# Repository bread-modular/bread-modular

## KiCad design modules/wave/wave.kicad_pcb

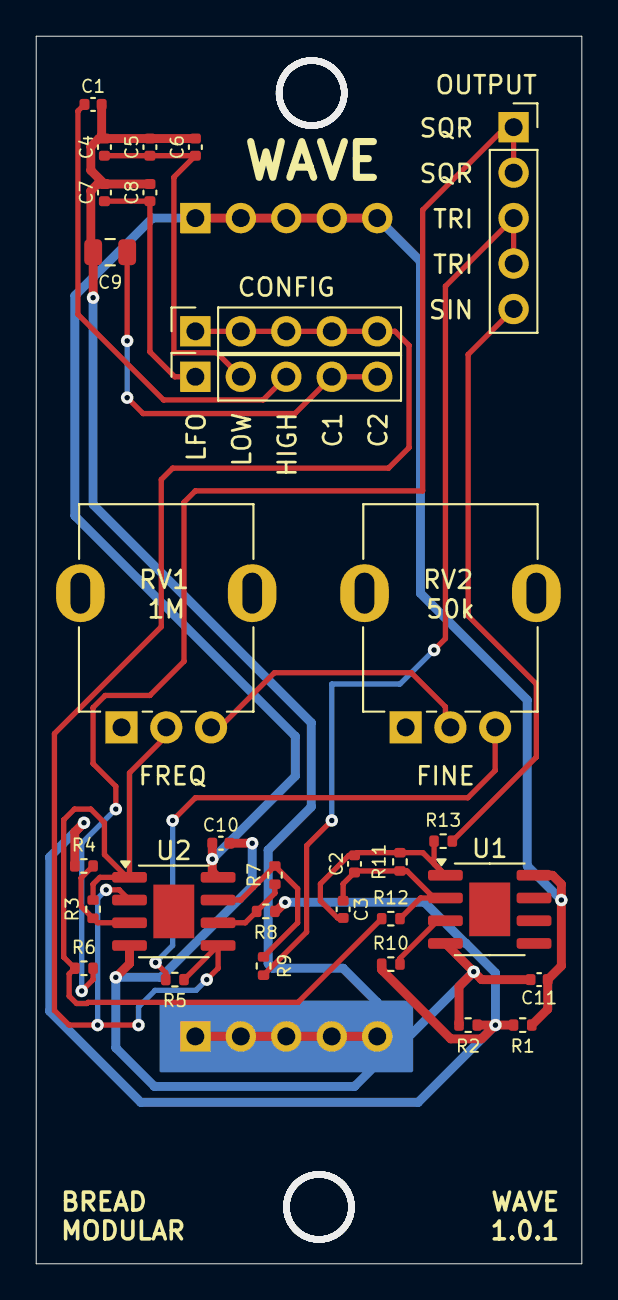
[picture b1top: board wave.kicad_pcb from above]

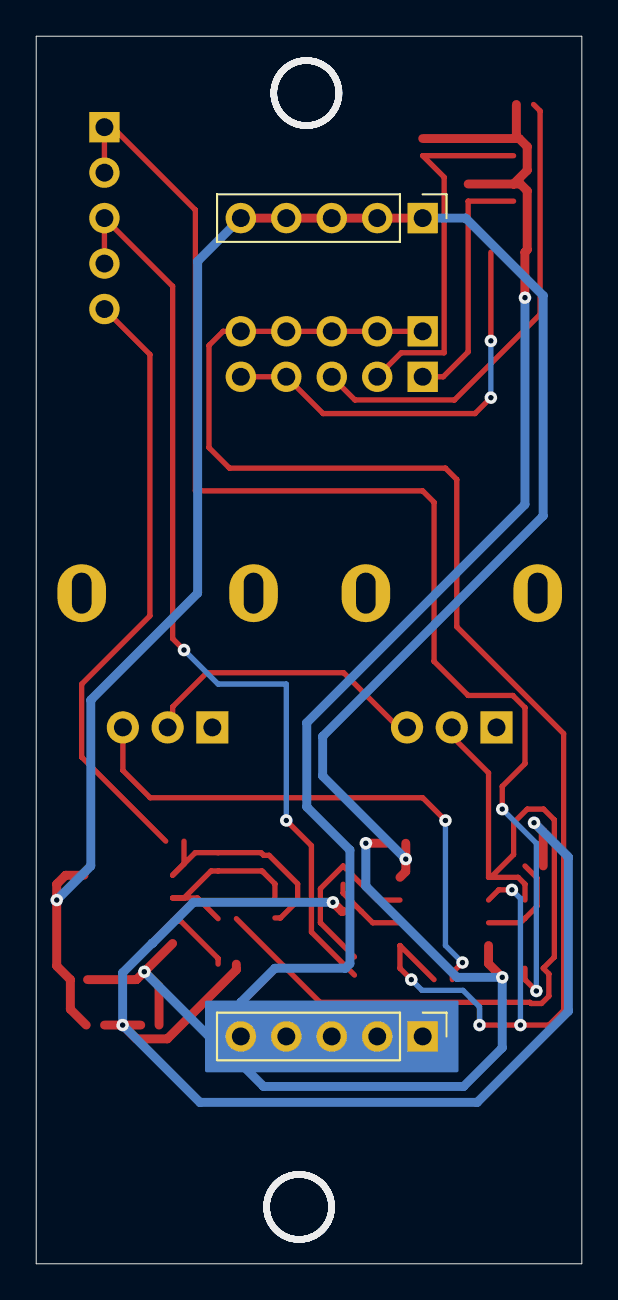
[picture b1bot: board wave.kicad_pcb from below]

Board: 2 copper layers, 30.5 x 68.6 mm, 33 parts (2 on the bottom side), 20 nets.

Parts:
5V1: Conn_01x05_Pin; PinHeader_1x05_P2.54mm_Vertical
C1: 1nf; C_0402_1005Metric
C2, C3, C10, C11: 0.1uf; C_0402_1005Metric
C4, C5, C6: 10nf; C_0402_1005Metric
C7, C8: 1uf; C_0402_1005Metric
C9: 22uf; C_0805_2012Metric
GND1: Conn_01x05_Pin; PinHeader_1x05_P2.54mm_Vertical
INPUT1: Cap Connect; PinSocket_1x05_P2.54mm_Vertical
INPUT2: Caps; PinSocket_1x05_P2.54mm_Vertical
OUTPUT2: Output Waves; PinSocket_1x05_P2.54mm_Vertical
R1, R2, R6, R9, R13: 1k; R_0402_1005Metric
R3, R4, R7, R8, R10, R11: 100k; R_0402_1005Metric
R5, R12: 10k; R_0402_1005Metric
RV1: 1M; Potentiometer_RV09
RV2: 50k; Potentiometer_RV09
U1, U2: MCP6002-xSN; SOIC-8-1EP_3.9x4.9mm_P1.27mm_EP2.29x3mm

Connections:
+2.5V: R1.2, R2.1, R4.1, R8.1, R10.1
+5V: 5V1.1, 5V1.2, 5V1.3, 5V1.4, 5V1.5, C10.1, C11.1, R1.1, U1.8 (V+), U2.8 (V+)
CAP_CONNECT: INPUT1.1, INPUT1.2, INPUT1.3, INPUT1.4, INPUT1.5, R5.1, U2.2 (-), U2.5 (+)
CAP_CUSTOM: C9.1, INPUT2.4, INPUT2.5
CAP_HIGH: C1.1, INPUT2.3
CAP_LFO: C7.1, C8.1, INPUT2.1
CAP_LOW: C4.1, C5.1, C6.1, INPUT2.2
GND: C1.2, C4.2, C5.2, C6.2, C7.2, C8.2, C9.2, C10.2, C11.2, GND1.1, GND1.2, GND1.3, GND1.4, GND1.5, R2.2, U1.4 (V-), U2.4 (V-)
unnamed: C2.2, C3.2, R11.2, R13.1, U1.1
unnamed: R5.2, RV2.3
unnamed: R7.2, R9.1, U2.7
unnamed: RV1.3, RV2.2
unnamed: R10.2, U1.3 (+)
unnamed: C2.1, C3.1, R11.1, R12.2, U1.2 (-)
unnamed: R3.1, R4.2, U2.3 (+)
unnamed: R7.1, R8.2, U2.6 (-)
OPAMP_SQUARE: R3.2, R6.1, R12.1, RV1.2, U2.1
OUT_SINE: OUTPUT2.5, R13.2
OUT_SQUARE: OUTPUT2.1, OUTPUT2.2, R6.2
OUT_TRI: OUTPUT2.3, OUTPUT2.4, R9.2

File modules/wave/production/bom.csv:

Designator,Footprint,Quantity,Value,LCSC Part #
"5V1, GND1",PinHeader_1x05_P2.54mm_Vertical,2,Conn_01x05_Pin,
C1,0402,1,1nf,
"C10, C11, C2, C3",0402,4,0.1uf,
"C4, C5, C6",0402,3,10nf,
"C7, C8",0402,2,1uf,
C9,0805,1,22uf,
INPUT1,PinSocket_1x05_P2.54mm_Vertical,1,Cap Connect,
INPUT2,PinSocket_1x05_P2.54mm_Vertical,1,Caps,
OUTPUT2,PinSocket_1x05_P2.54mm_Vertical,1,Output Waves,
"R1, R13, R2, R6, R9",0402,5,1k,
"R10, R11, R3, R4, R7, R8",0402,6,100k,
"R12, R5",0402,2,10k,
RV1,Potentiometer_RV09,1,1M,
RV2,Potentiometer_RV09,1,50k,
"U1, U2",SOIC-8-1EP_3.9x4.9mm_P1.27mm_EP2.29x3mm,2,MCP6002-xSN,

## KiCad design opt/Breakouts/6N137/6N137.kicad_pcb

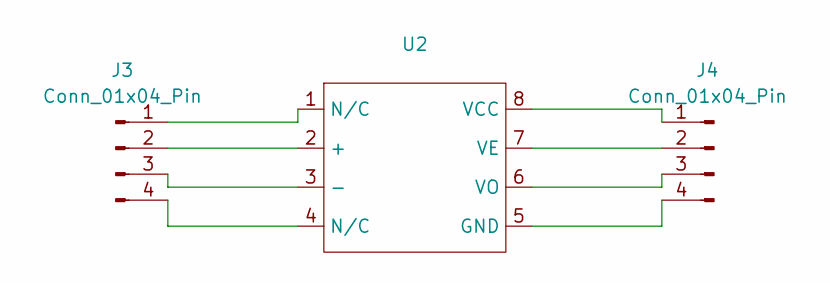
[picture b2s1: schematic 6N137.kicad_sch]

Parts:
J3, J4: Conn_01x04_Pin; PinSocket_1x04_P2.54mm_Vertical
U2: SOIC-8 2.54

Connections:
unnamed: J3.1, U2.1 (N/C)
unnamed: J3.2, U2.2 (+)
unnamed: J3.3, U2.3 (-)
unnamed: J3.4, U2.4 (N/C)
unnamed: J4.1, U2.8 (VCC)
unnamed: J4.2, U2.7 (VE)
unnamed: J4.3, U2.6 (VO)
unnamed: J4.4, U2.5 (GND)

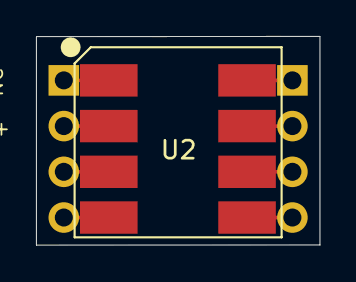
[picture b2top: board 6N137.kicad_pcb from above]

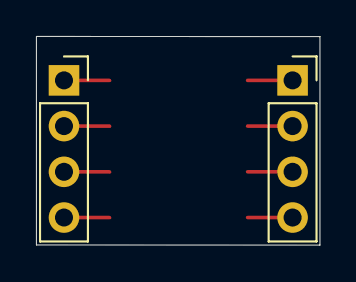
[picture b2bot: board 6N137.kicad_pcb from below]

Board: 2 copper layers, 15.8 x 11.6 mm, 3 parts (2 on the bottom side), 8 nets.

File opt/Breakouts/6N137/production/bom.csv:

Designator,Footprint,Quantity,Value,LCSC Part #
"J3, J4",PinSocket_1x04_P2.54mm_Vertical,2,Conn_01x04_Pin,
U2,SOIC-8 2.54,1,~,

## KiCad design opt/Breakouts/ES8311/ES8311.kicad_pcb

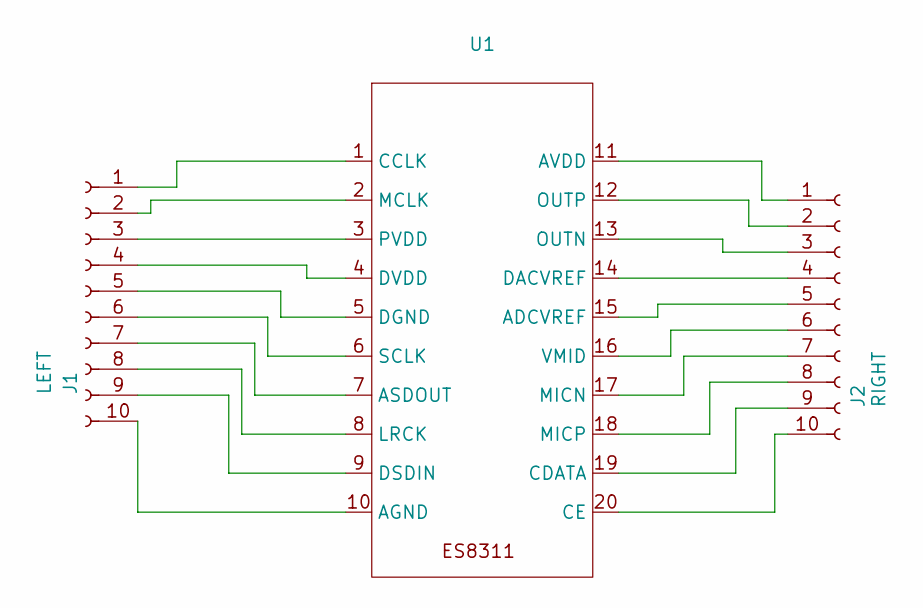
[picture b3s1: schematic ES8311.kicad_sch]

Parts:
J1: LEFT; PinSocket_1x10_P2.54mm_Vertical
J2: RIGHT; PinSocket_1x10_P2.54mm_Vertical
U1: QFN-20-1EP_3x3mm_P0.4mm_EP1.65x1.65mm

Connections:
unnamed: J1.1, U1.1 (CCLK)
unnamed: J1.2, U1.2 (MCLK)
unnamed: J1.3, U1.3 (PVDD)
unnamed: J1.4, U1.4 (DVDD)
unnamed: J1.5, U1.5 (DGND)
unnamed: J1.6, U1.6 (SCLK)
unnamed: J1.7, U1.7 (ASDOUT)
unnamed: J1.8, U1.8 (LRCK)
unnamed: J1.9, U1.9 (DSDIN)
unnamed: J1.10, U1.10 (AGND)
unnamed: J2.1, U1.11 (AVDD)
unnamed: J2.2, U1.12 (OUTP)
unnamed: J2.3, U1.13 (OUTN)
unnamed: J2.4, U1.14 (DACVREF)
unnamed: J2.5, U1.15 (ADCVREF)
unnamed: J2.6, U1.16 (VMID)
unnamed: J2.7, U1.17 (MICN)
unnamed: J2.8, U1.18 (MICP)
unnamed: J2.9, U1.19 (CDATA)
unnamed: J2.10, U1.20 (CE)

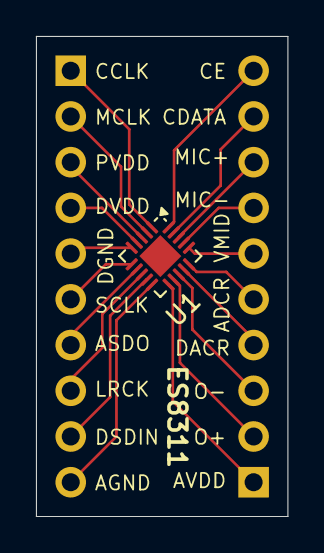
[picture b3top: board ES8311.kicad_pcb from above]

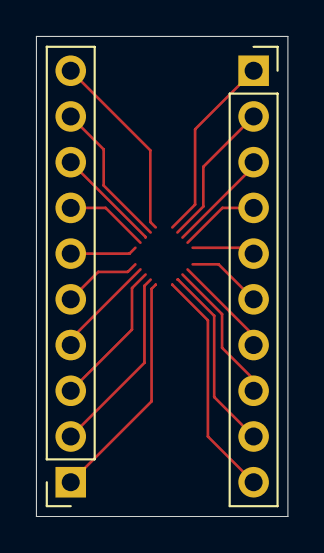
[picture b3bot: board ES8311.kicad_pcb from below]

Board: 2 copper layers, 14.0 x 26.7 mm, 3 parts (2 on the bottom side), 20 nets.

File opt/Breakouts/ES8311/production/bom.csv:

Designator,Footprint,Quantity,Value,LCSC Part #
J1,PinSocket_1x10_P2.54mm_Vertical,1,LEFT,
J2,PinSocket_1x10_P2.54mm_Vertical,1,RIGHT,
U1,QFN-20-1EP_3x3mm_P0.4mm_EP1.65x1.65mm,1,~,

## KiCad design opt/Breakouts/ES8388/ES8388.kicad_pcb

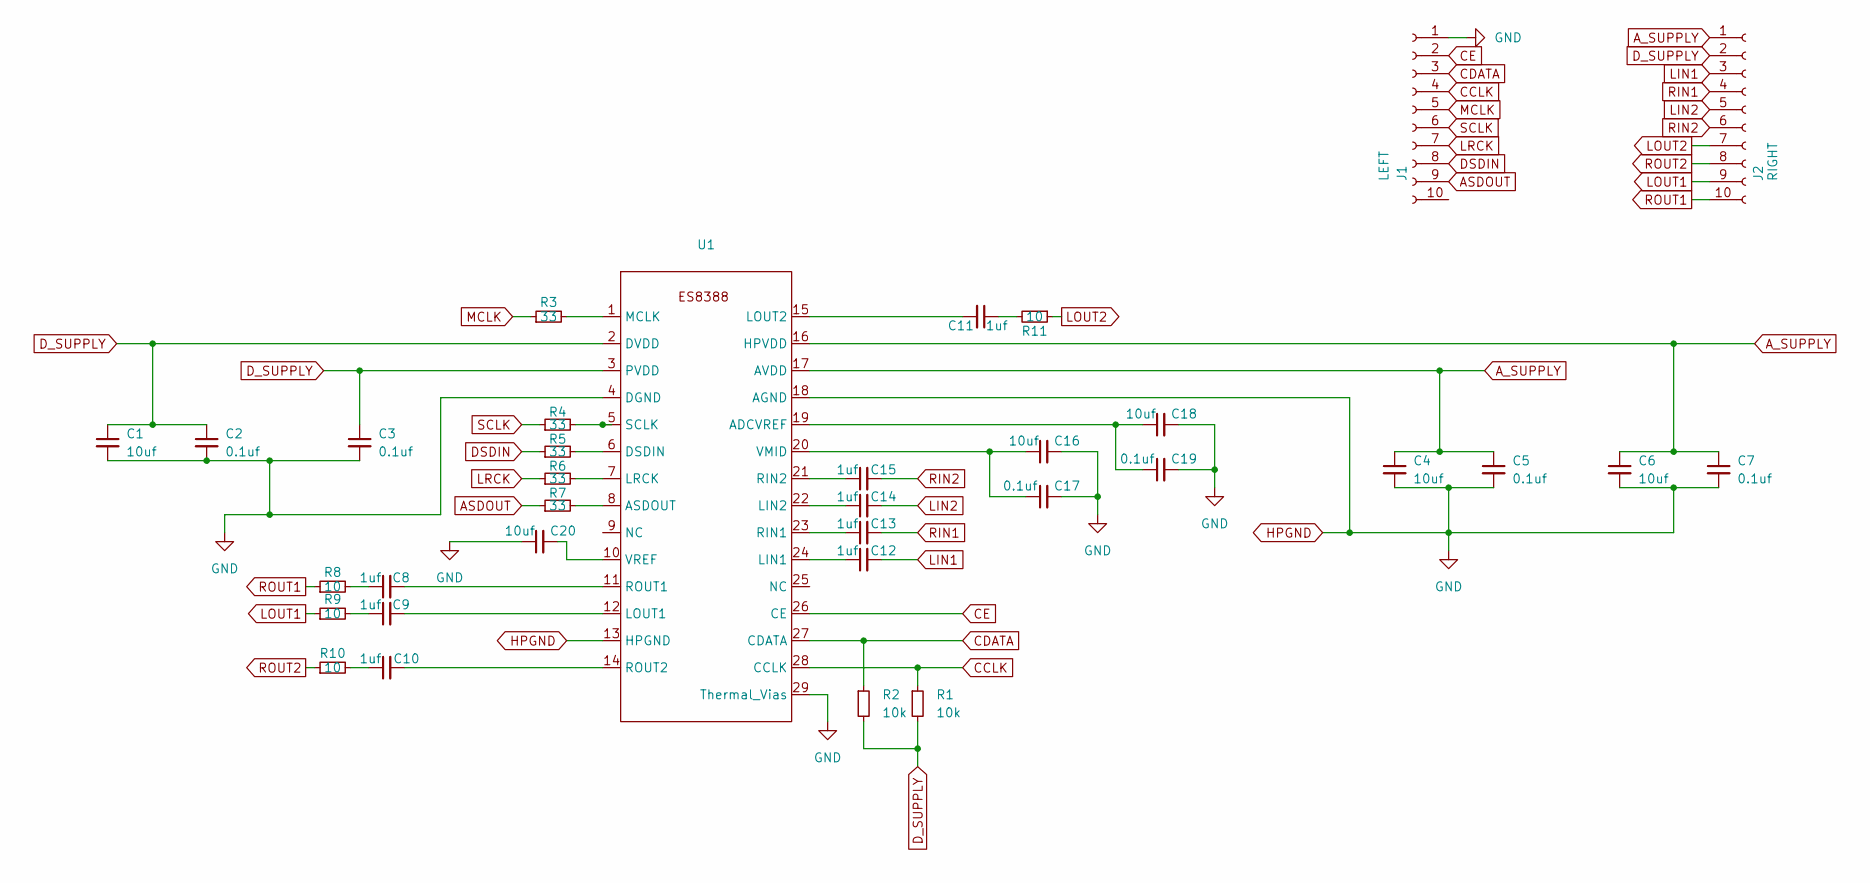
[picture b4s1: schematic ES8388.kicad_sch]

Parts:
C1, C4, C6, C16, C18, C20: 10uf; C_0402_1005Metric
C2, C3, C5, C7, C17, C19: 0.1uf; C_0402_1005Metric
C8, C9, C10, C11, C12, C13, C14, C15: 1uf; C_0402_1005Metric
J1: LEFT; PinSocket_1x10_P2.54mm_Vertical
J2: RIGHT; PinSocket_1x10_P2.54mm_Vertical
R1, R2: 10k; R_0402_1005Metric
R3, R4, R5, R6, R7: 33; R_0402_1005Metric
R8, R9, R10, R11: 10; R_0402_1005Metric
U1: QFN-28-1EP_4x4mm_P0.45mm_EP2.4x2.4mm_ThermalVias

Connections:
ASDOUT: J1.9, R7.1
A_SUPPLY: C4.1, C5.1, C6.1, C7.1, J2.1, U1.16 (HPVDD), U1.17 (AVDD)
CCLK: J1.4, R1.1, U1.28 (CCLK)
CDATA: J1.3, R2.1, U1.27 (CDATA)
CE: J1.2, U1.26 (CE)
DSDIN: J1.8, R5.1
D_SUPPLY: C1.1, C2.1, C3.1, J2.2, R1.2, R2.2, U1.2 (DVDD), U1.3 (PVDD)
HPGND: C1.2, C2.2, C3.2, C4.2, C5.2, C6.2, C7.2, C16.2, C17.2, C18.2, C19.2, C20.1, J1.1, U1.4 (DGND), U1.13 (HPGND), U1.18 (AGND), U1.29 (Thermal_Vias)
LIN1: C12.2, J2.3
LIN2: C14.2, J2.5
LOUT1: J2.9, R9.1
LOUT2: J2.7, R11.1
LRCK: J1.7, R6.1
MCLK: J1.5, R3.1
unnamed: C8.1, R8.2
unnamed: C9.1, R9.2
unnamed: C10.1, R10.2
unnamed: C11.1, R11.2
unnamed: C18.1, C19.1, U1.19 (ADCVREF)
unnamed: R7.2, U1.8 (ASDOUT)
unnamed: R5.2, U1.6 (DSDIN)
unnamed: C12.1, U1.24 (LIN1)
unnamed: C14.1, U1.22 (LIN2)
unnamed: C9.2, U1.12 (LOUT1)
unnamed: C11.2, U1.15 (LOUT2)
unnamed: R6.2, U1.7 (LRCK)
unnamed: R3.2, U1.1 (MCLK)
unnamed: C13.1, U1.23 (RIN1)
unnamed: C15.1, U1.21 (RIN2)
unnamed: C8.2, U1.11 (ROUT1)
unnamed: C10.2, U1.14 (ROUT2)
unnamed: R4.2, U1.5 (SCLK)
unnamed: C16.1, C17.1, U1.20 (VMID)
unnamed: C20.2, U1.10 (VREF)
RIN1: C13.2, J2.4
RIN2: C15.2, J2.6
ROUT1: J2.10, R8.1
ROUT2: J2.8, R10.1
SCLK: J1.6, R4.1

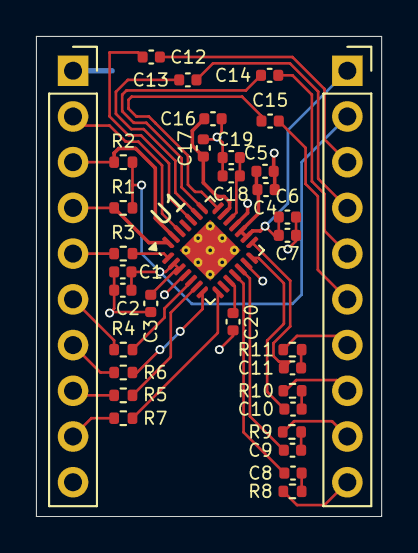
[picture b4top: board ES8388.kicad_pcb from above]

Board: 2 copper layers, 19.2 x 26.7 mm, 34 parts (0 on the bottom side), 39 nets.

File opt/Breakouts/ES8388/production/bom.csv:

Designator,Footprint,Quantity,Value,LCSC Part #
"C1, C16, C18, C20, C4, C6",0402,6,10uf,
"C10, C11, C12, C13, C14, C15, C8, C9",0402,8,1uf,
"C17, C19, C2, C3, C5, C7",0402,6,0.1uf,
J1,PinSocket_1x10_P2.54mm_Vertical,1,LEFT,
J2,PinSocket_1x10_P2.54mm_Vertical,1,RIGHT,
"R1, R2",0402,2,10k,
"R10, R11, R8, R9",0402,4,10,
"R3, R4, R5, R6, R7",0402,5,33,
U1,QFN-28-1EP_4x4mm_P0.45mm_EP2.4x2.4mm_ThermalVias,1,~,

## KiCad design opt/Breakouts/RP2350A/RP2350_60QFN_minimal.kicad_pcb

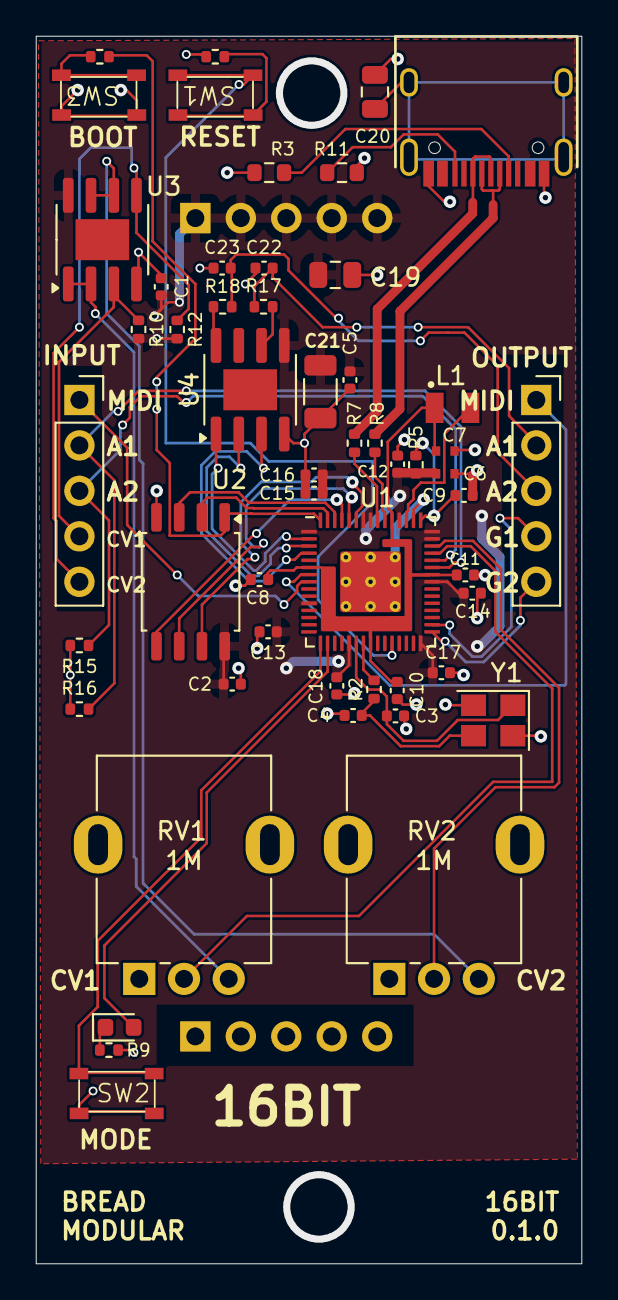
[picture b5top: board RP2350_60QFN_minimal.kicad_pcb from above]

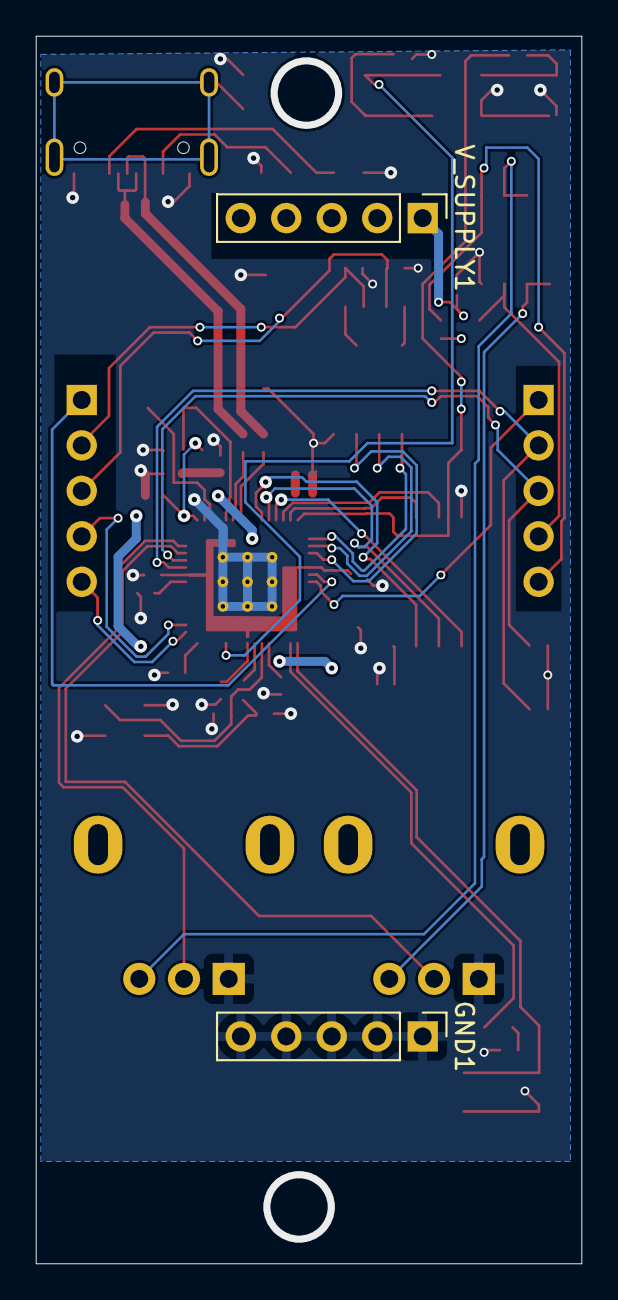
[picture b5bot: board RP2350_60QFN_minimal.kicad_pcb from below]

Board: 2 copper layers, 30.5 x 68.6 mm, 55 parts (2 on the bottom side), 47 nets.

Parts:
C1, C5: 0.1uf; C_0402_1005Metric
C2, C8, C11, C12, C13, C14, C15, C16, C17, C18: 100n; C_0402_1005Metric
C3, C4: 15p; C_0402_1005Metric
C6, C7: 4.7u; C_0402_1005Metric_small_pads
C9, C10: 4.7u; C_0402_1005Metric
C19: 10u; C_0805_2012Metric
C20: 10nf; C_0805_2012Metric
C21: 100uf; C_1206_3216Metric
C22, C23: 10nf; C_0402_1005Metric
D1: LED; LED_0603_1608Metric
GND1: Conn_01x05_Pin; PinHeader_1x05_P2.54mm_Vertical
J1, J2: Conn_01x08_Socket; PinSocket_1x05_P2.54mm_Vertical
J5: USB_C_Receptacle_USB2.0_14P; HRO-TYPE-C-31-M-12
L1: AOTA-B201610S3R3-101-T; L_pol_2016
R2, R4, R6, R9: 1k; R_0402_1005Metric
R3, R11: 5.1k; R_0603_1608Metric
R5: 33; R_0402_1005Metric
R7, R8: 27; R_0402_1005Metric
R10, R12, R15, R16: 100k; R_0402_1005Metric
R17, R18: 10k; R_0402_1005Metric
RV1, RV2: 1M; Potentiometer_RV09
SW1, SW2, SW3: K2-1808SN-A4SW-01
U1: RP2350_60QFN; RP2350-QFN-60-1EP_7x7_P0.4mm_EP3.4x3.4mm_ThermalVias
U2: W25Q128JVS; SOIC-8_5.23x5.23mm_P1.27mm
U3: MCP6002-xSN; SOIC-8-1EP_3.9x4.9mm_P1.27mm_EP2.29x3mm
U4: PT8211; SOIC-8-1EP_3.9x4.9mm_P1.27mm_EP2.29x3mm
V_SUPPLY1: Conn_01x05_Pin; PinHeader_1x05_P2.54mm_Vertical
Y1: ABM8-272-T3; Crystal_SMD_3225-4Pin_3.2x2.5mm

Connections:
+1V1: C7.1, C8.1, C10.1, C11.1, L1.1, U1.6 (DVDD), U1.23 (DVDD), U1.39 (DVDD), U1.50 (VREG_FB)
+3V3: C1.1, C2.1, C5.1, C6.1, C12.1, C13.1, C14.1, C15.1, C16.1, C17.1, C18.1, C19.1, C21.1, R5.1, R10.1, R12.1, U1.1 (IOVDD), U1.11 (IOVDD), U1.20 (IOVDD), U1.30 (IOVDD), U1.38 (IOVDD), U1.44 (ADC_AVDD), U1.45 (IOVDD), U1.49 (VREG_VIN), U1.53 (USB_OTP_VDD), U1.54 (QSPI_IOVDD), U2.8 (VCC), U3.8 (V+), U4.5 (VDD), V_SUPPLY1.1, V_SUPPLY1.2, V_SUPPLY1.3, V_SUPPLY1.4, V_SUPPLY1.5
/GPIO12: SW2.1 (A), U1.16 (GPIO12)
/GPIO13: D1.2 (A), U1.17 (GPIO13)
/QSPI_SCLK: U1.56 (QSPI_SCLK), U2.6 (CLK)
/QSPI_SD0: U1.57 (QSPI_SD0), U2.5 (DI(IO0))
/QSPI_SD1: U1.59 (QSPI_SD1), U2.2 (DO(IO1))
/QSPI_SD2: U1.58 (QSPI_SD2), U2.3 (IO2)
/QSPI_SD3: U1.55 (QSPI_SD3), U2.7 (IO3)
/RUN: SW1.2 (B), U1.26 (RUN)
/VREG_AVDD: C9.1, R5.2, U1.46 (VREG_AVDD)
/VREG_LX: L1.2, U1.48 (VREG_LX)
/XIN: C3.1, U1.21 (XIN), Y1.1
/XOUT: R2.1, U1.22 (XOUT)
/~USB_BOOT: R6.2, SW3.2 (B)
AIN_1: J1.2, R16.2, U1.40 (GPIO26_ADC0)
AIN_2: J1.3, R15.1, U1.41 (GPIO27_ADC1)
AOUT_1: C22.2, J2.2, R17.1
AOUT_2: C23.2, J2.3, R18.1
BCK: U1.2 (GPIO0), U4.1 (BCK)
BUFF_CV1: RV1.2, U1.42 (GPIO28_ADC2)
BUFF_CV2: RV2.2, U1.43 (GPIO29_ADC3)
CV1: J1.4, R10.2, U3.3 (+)
CV2: J1.5, R12.2, U3.5 (+)
DIN: U1.4 (GPIO2), U4.3 (DIN)
GND: C1.2, C2.2, C3.2, C4.2, C5.2, C6.2, C7.2, C8.2, C9.2, C10.2, C11.2, C12.2, C13.2, C14.2, C15.2, C16.2, C17.2, C18.2, C19.2, C20.2, C21.2, C22.1, C23.1, GND1.1, GND1.2, GND1.3, GND1.4, GND1.5, J5.A1 (GND), J5.A12 (GND), R3.2, R4.2, R9.1, R11.2, R15.2, R16.1, RV1.1, RV2.1, SW2.2 (B), SW3.1 (A), U1.47 (VREG_PGND), U1.61 (GND), U2.4 (GND), U3.4 (V-), U4.4 (GND), Y1.2, Y1.4
GOUT_1: J2.4, U1.32 (GPIO20)
GOUT_2: J2.5, U1.31 (GPIO19)
MIDI_IN: J1.1, U1.8 (GPIO5)
MIDI_OUT: J2.1, U1.7 (GPIO4)
unnamed: C4.1, R2.2, Y1.3
unnamed: D1.1 (K), R9.2
unnamed: J5.A5 (CC1), R3.1
unnamed: J5.B5 (CC2), R11.1
unnamed: C20.1, J5.S1 (SHIELD)
unnamed: J5.A4 (VBUS), J5.A9 (VBUS)
unnamed: R4.1, SW1.1 (A)
unnamed: R8.2, U1.51 (USB_DM)
unnamed: R7.2, U1.52 (USB_DP)
unnamed: RV1.3, U3.1, U3.2 (-)
unnamed: RV2.3, U3.6 (-), U3.7
unnamed: R17.2, U4.6 (L)
unnamed: R18.2, U4.8 (R)
QSPI_SS: R6.1, U1.60 (QSPI_SS), U2.1 (~CS)
USB_D+: J5.A6 (D+), J5.B6 (D+), R7.1
USB_D-: J5.A7 (D-), J5.B7 (D-), R8.1
WS: U1.3 (GPIO1), U4.2 (WS)

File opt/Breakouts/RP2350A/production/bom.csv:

Designator,Footprint,Quantity,Value,LCSC Part #
"C1, C5",0402,2,0.1uf,
"C10, C6, C7, C9",0402,4,4.7u,
"C11, C12, C13, C14, C15, C16, C17, C18, C2, C8",0402,10,100n,
C19,0805,1,10u,
C20,0805,1,10nf,
C21,1206,1,100uf,
"C22, C23",0402,2,10nf,
"C3, C4",0402,2,15p,
D1,0603,1,LED,
"GND1, V_SUPPLY1",PinHeader_1x05_P2.54mm_Vertical,2,Conn_01x05_Pin,
"J1, J2",PinSocket_1x05_P2.54mm_Vertical,2,Conn_01x08_Socket,
J5,HRO-TYPE-C-31-M-12,1,USB_C_Receptacle_USB2.0_14P,
L1,L_pol_2016,1,AOTA-B201610S3R3-101-T,
"R10, R12, R15, R16",0402,4,100k,
"R11, R3",0603,2,5.1k,
"R17, R18",0402,2,10k,
"R2, R4, R6, R9",0402,4,1k,
R5,0402,1,33,
"R7, R8",0402,2,27,
"RV1, RV2",Potentiometer_RV09,2,1M,
"SW1, SW2, SW3",K2-1808SN-A4SW-01,3,K2-1808SN-A4SW-01,
U1,RP2350-QFN-60-1EP_7x7_P0.4mm_EP3.4x3.4mm_ThermalVias,1,RP2350_60QFN,
U2,SOIC-8_5.23x5.23mm_P1.27mm,1,W25Q128JVS,
U3,SOIC-8-1EP_3.9x4.9mm_P1.27mm_EP2.29x3mm,1,MCP6002-xSN,
U4,SOIC-8-1EP_3.9x4.9mm_P1.27mm_EP2.29x3mm,1,PT8211,
Y1,Crystal_SMD_3225-4Pin_3.2x2.5mm,1,ABM8-272-T3,

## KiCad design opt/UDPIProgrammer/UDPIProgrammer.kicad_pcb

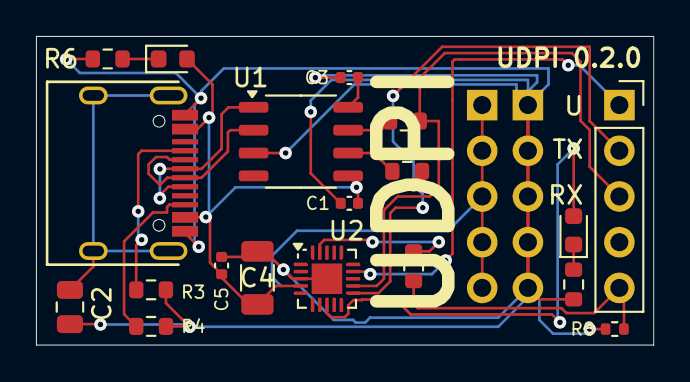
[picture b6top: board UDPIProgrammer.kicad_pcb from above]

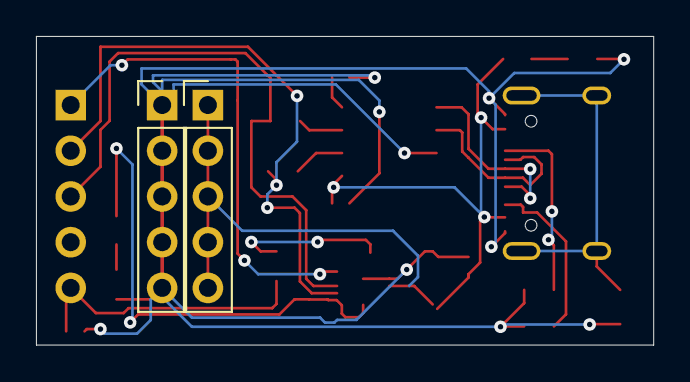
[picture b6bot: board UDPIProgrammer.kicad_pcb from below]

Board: 2 copper layers, 34.3 x 17.1 mm, 21 parts (2 on the bottom side), 19 nets.

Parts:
C1, C3: 0.1uf; C_0402_1005Metric
C2: 10nf; C_0805_2012Metric
C4: 100uf; C_1206_3216Metric
C5: 100nf; C_0402_1005Metric
D1, D2: LED; LED_0603_1608Metric
GND1: Conn_01x05_Pin; PinHeader_1x05_P2.54mm_Vertical
J2: USB_C_Receptacle_USB2.0_14P; HRO-TYPE-C-31-M-12
OUTPUT1: Conn_01x05_Socket; PinSocket_1x05_P2.54mm_Vertical
R1, R2, R6, R7: 1k; R_0603_1608Metric
R3, R4: 5.1k; R_0603_1608Metric
R5: 4.7k; R_0603_1608Metric
R8: 100k; R_0402_1005Metric
U1: CH340N; SOP-8_3.9x4.9mm_P1.27mm
U2: ATtiny1616-M; VQFN-20-1EP_3x3mm_P0.4mm_EP1.7x1.7mm
VSUPPLY1: Conn_01x05_Pin; PinHeader_1x05_P2.54mm_Vertical

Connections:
5V: C1.1, C4.2, C5.2, D1.2 (A), J2.A4 (VBUS), J2.A9 (VBUS), U1.5 (VCC), U2.4 (VCC)
+3.3V: VSUPPLY1.1, VSUPPLY1.2, VSUPPLY1.3, VSUPPLY1.4, VSUPPLY1.5
D+: J2.A6 (D+), J2.B6 (D+), U1.1 (UD+)
D-: J2.A7 (D-), J2.B7 (D-), U1.2 (UD-)
GND: C1.2, C2.2, C3.1, C4.1, C5.1, GND1.1, GND1.2, GND1.3, GND1.4, GND1.5, J2.A1 (GND), J2.A12 (GND), R3.2, R4.2, R6.2, R7.2, R8.2, U1.3 (GND), U2.3 (GND), U2.21 (GND)
LED: D2.2 (A), U2.8 (PA7)
MCU_UDPI: OUTPUT1.5, R5.2, R8.1
unnamed: D1.1 (K), R6.1
unnamed: D2.1 (K), R7.1
unnamed: J2.A5 (CC1), R3.1
unnamed: J2.B5 (CC2), R4.1
unnamed: C2.1, J2.S1 (SHIELD)
unnamed: R2.1, U1.7 (RXD)
unnamed: R1.1, U1.6 (TXD)
unnamed: C3.2, U1.8 (V3)
unnamed: R5.1, U2.19 (~RESET/PA0)
PROG: OUTPUT1.1, U2.14 (PB0)
SERIAL_RX: OUTPUT1.3, R2.2, U2.12 (PB2)
SERIAL_TX: OUTPUT1.2, R1.2, U2.11 (PB3)

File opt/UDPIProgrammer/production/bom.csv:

Designator,Footprint,Quantity,Value,LCSC Part #
"C1, C3",0402,2,0.1uf,
C2,0805,1,10nf,
C4,1206,1,100uf,
C5,0402,1,100nf,
"D1, D2",0603,2,LED,
"GND1, VSUPPLY1",PinHeader_1x05_P2.54mm_Vertical,2,Conn_01x05_Pin,
J2,HRO-TYPE-C-31-M-12,1,USB_C_Receptacle_USB2.0_14P,
OUTPUT1,PinSocket_1x05_P2.54mm_Vertical,1,Conn_01x05_Socket,
"R1, R2, R6, R7",0603,4,1k,
"R3, R4",0603,2,5.1k,
R5,0603,1,4.7k,
R8,0402,1,100k,
U1,SOP-8_3.9x4.9mm_P1.27mm,1,CH340N,
U2,VQFN-20-1EP_3x3mm_P0.4mm_EP1.7x1.7mm,1,ATtiny1616-M,
